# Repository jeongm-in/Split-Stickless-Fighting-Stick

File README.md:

# Split Stickless Fighting Game Controller - Version 1
- Most commercial fighting game controllers all have very "crowded" layout. I wanted to make something that gives ample space between my left and right hands, and also learn how to design PCB from scratch. 

# Design 
- Split between left (Movement) and right (Other controls)
- Followed [ai03's PCB Design](https://wiki.ai03.com/books/pcb-design) guide for the KiCad part
- Uses RJ45 (Commonly used in Ethernet cables) to connect both sides 
    - TRRS Cables (Commonly used in headphone jacks with microphone) are usually used in split keyboards, but this only supports up to 4 connections.
    - I needed minimum 5 pins (UP, LEFT, RIGHT, DOWN, and GND) on the Left, so I had to use something with more connections. 
    - May explore with different connector in future revisions (USB Type C?)
- Uses GP2040-CE and has all the button mappings of a PS4 controller. So this could maybe "tournament legal", though I don't intend to use this in contests
- Also hotswappable! Bring any keyboard switch you want 

# Pin layout 

| GPIO Pin | Button | GPIO Pin  | Button |
| --- | --- | --- | --- |
| 00 | A1 (Capture) | 15 | L3 (LS) |
| 01 | Down | 16 | R3 (RS) | 
| 02 | A2 (Home) | 17 | R2 (RT) | 
| 03 | Up | 18 | L2 (LT) | 
| 04 | Right | 19 | B2 | 
| 05 | Left | 20 | B1 | 
| 06 | None | 21 | None | 
| 07 | None | 22 | R1 (RB) | 
| 08 | S2 (Share) | 23 | None | 
| 09 | None | 24 | None | 
| 10 | None | 25 | None | 
| 11 | None | 26 | L1 (LB) | 
| 12 | None | 27 | B4 | 
| 13 | S1 (Option) | 28 | B3 | 
| 14 | None | 29 | None |

* See [Documentation](https://gp2040-ce.info/usage) for button mappings

* Also see [Config](https://github.com/jeongm-in/Split-Stickless-Fighting-Stick/blob/main/Config/gp2040ce_backup_20240914181731127.gp2040) directory to download the config file that can be loaded in GP2040-CE

# Parts 
- 1 Raspberry Pi Pico
- 2 Amphenol RJHSE-5380 (8P8C RJ45 female adapter)
- 4 Omron B3F-1020 switches (or any B3F-10x)
- 12 Cherry MX compatible switches of your choice 
- 12 Kailh Hotswap sockets
- 12 Keycaps of your choice

# PCB Design
Front

Back

# Assembly 
Finally got all the parts in mail and assembled the board. V-Cut groove was very easy to split.

And then soldered the components onto the board. Pi Pico I got was very hard to solder properly, but I managed to get everything done without shorting anything. 

After the assembly, I installed GP2040-CE firmware and tested every button is working as expected. Since I changed the pins for easy routing, my layout is different from the out of the box default. 

Luckily I somehow soldered everything fine and it worked perfectly. Put on some keycaps from my "Mechanical Keyboard days" for fun.

It is a little awkward so I'll need some time to get used to it, but I'm glad it all works correctly. Hotswap sockets are surprisingly sturdy and I don't think I would even need a face plate to hold the switches in place. I would still need some spacers with rubber feet to prevent boards from moving around, but it is ready for use now. 

Overall this was a very fun project, I'm glad I actually finished a project this time. I still have 4 more PCBs so I may assemble remainder when I get bored. Might also come back with V2 sometime in the future with more improvements. 

# ToDo 
- Exterior case / plate / feet for the board
- Rename KiCad project name from my-split to something meaningful

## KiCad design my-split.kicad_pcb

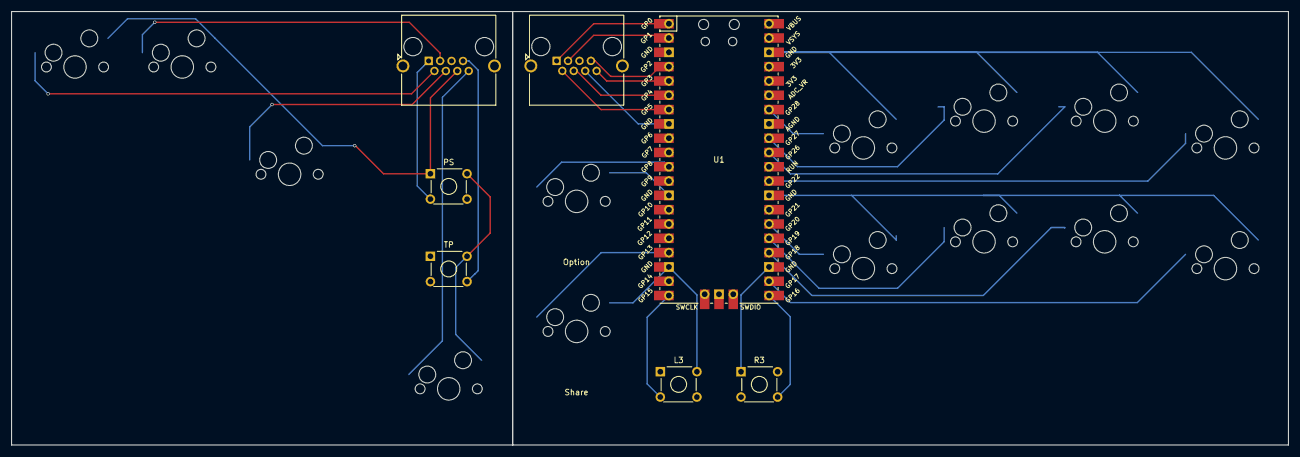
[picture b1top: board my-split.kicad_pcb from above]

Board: 2 copper layers, 226.7 x 77.0 mm, 21 parts (0 on the bottom side), 26 nets.

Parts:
J1, J3: 8P8C; RJ45_Amphenol_RJHSE5380
L3: SW_Omron_B3FS; SW_TH_Tactile_Omron_B3F-10xx
MX1, MX2, MX3, MX4, MX5, MX9, MX10, MX13, MX14, MX15, MX16, MX17, MX18, MX19: MX-NoLED; MXOnly-1U-Hotswap
PS: SW_Omron_B3FS; SW_TH_Tactile_Omron_B3F-10xx
R3: SW_Omron_B3FS; SW_TH_Tactile_Omron_B3F-10xx
TP: SW_Omron_B3FS; SW_TH_Tactile_Omron_B3F-10xx
U1: Pico; RPi_Pico_SMD_TH

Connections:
A1 - Home: J1.1, U1.1 (GPIO0)
A1 - Home - LEFT: J3.1, PS.2
A2 - Capture: J1.7, U1.4 (GPIO2)
A2 - Capture - LEFT: J3.7, TP.2
B1 - A: MX15.1 (COL), U1.26 (GPIO20)
B2 - B: MX16.1 (COL), U1.25 (GPIO19)
B3 - X: MX9.1 (COL), U1.34 (GPIO28_ADC2)
B4 - Y: MX10.1 (COL), U1.32 (GPIO27_ADC1)
DOWN: J1.3, U1.2 (GPIO1)
DOWN - LEFT: J3.3, MX3.1 (COL)
GND: J1.6, L3.1, MX1.2 (ROW), MX5.2 (ROW), MX9.2 (ROW), MX10.2 (ROW), MX13.2 (ROW), MX14.2 (ROW), MX15.2 (ROW), MX16.2 (ROW), MX17.2 (ROW), MX18.2 (ROW), R3.1, U1.3 (GND), U1.8 (GND), U1.13 (GND), U1.18 (GND), U1.23 (GND), U1.28 (GND), U1.38 (GND)
GND - LEFT: J3.6, MX2.2 (ROW), MX3.2 (ROW), MX4.2 (ROW), MX19.2 (ROW), PS.1, TP.1
L1 - LB: MX13.1 (COL), U1.31 (GPIO26_ADC0)
L2 - LT: MX17.1 (COL), U1.24 (GPIO18)
L3 - LS: L3.2, U1.20 (GPIO15)
LEFT: J1.2, U1.7 (GPIO5)
LEFT - LEFT: J3.2, MX2.1 (COL)
R1 - RB: MX14.1 (COL), U1.29 (GPIO22)
R2 - RT: MX18.1 (COL), U1.22 (GPIO17)
R3 - RS: R3.2, U1.21 (GPIO16)
RIGHT: J1.4, U1.6 (GPIO4)
RIGHT - LEFT: J3.4, MX4.1 (COL)
S1 - Share: MX5.1 (COL), U1.17 (GPIO13)
S2 - Options: MX1.1 (COL), U1.11 (GPIO8)
UP: J1.8, U1.5 (GPIO3)
UP - LEFT: J3.8, MX19.1 (COL)

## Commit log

2024-03-10 Publish project on GitHub
2024-03-10 Apply .gitignore changes
2024-03-10 Add an entry to ToDo list
2024-03-11 Update design per review from the PCB manufacturer
2024-03-19 Add more photos and wrap up the project
2024-09-14 Add firmware file for key mappings
2024-09-14 Update README; add blurb about firmware file
2024-09-14 Rename firmware directory
